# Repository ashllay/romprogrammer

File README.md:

# romprogrammer
Open Source Flash/EEPROM programmer

This is an open source programmer for 8 bit-wide parallel Flash/EEPROM chips. So far I've only tested it with (and hardcoded the software for) 2MBit (256Kx8) JEDEC compatible Flash chips (and designed the board layout accordingly).

Larger ROMs would require a redesign of the board, smaller ROMs require an adapter for the pinout.

The board uses an Arduino Nano onto which the firmware is flashed. Then you can read and write your PROMs using the command line tool (which should work on all POSIX systems, but I only tested on Debian Linux).

The board layout is single sided and uses relatively wide clearances and traces - ideal for DIY etching :)

## Schematic and Layout

Schematic and layout were made in [KiCad EDA](http://kicad-pcb.org/). You can use that to export to Gerber or PDF, whatever you prefer for you etching (or what you need for your professional board manufacturing service).

## Building

### Hardware
#### Parts

* Whatever PCB material you want to use
* 3x 74HC595 serial in, parallel out shift registers (Dual Inline Package)
* 1x 32 Pin JEDEC DIL chip socket (ZIF, if you want to make your life easier)
* 2x 15 Pin female pin headers (for the Arduino Nano)
* 1x Arduino Nano
* 1x 100nF ceramic capacitor, through hole
* a few centimeters of insulated jumper wire

The hardware is designed to be easily DIY etched. It only uses a single layer (+ a few jumper wires). The jumper wires are indicated on the front copper layer. You should also add a 100nF ceramic cap between pins 16 and 32 of the ROM socket to stabilize its power supply.

### Software
The software is split into two parts, the firmware for the ATMega328P (the µC on the Arduino Nano) and the Linux command line tool. 

#### Firmware

The firmware requires gcc-avr and [avr-libc](http://www.nongnu.org/avr-libc/). The Makefile also contains a rule for writing the firmware to the Arduino using avrdude. (Using an AVRISPmk2, if you want to use the built-in bootloader of the Arduino, you'll have to adapt the Makefile accordingly).

Just build the software in the firmware directory using make, flash it using make flash.

#### CLI

The Linux command line tool is compiled using CMake, goto the cli directory, create a build directory, cd into it, run cmake, then make:

```
mkdir build
cd build
cmake ..
make
```

### Usage
#### Basic Usage and Tests

The command line interface is relatively easy to use, because it doesn't offer many functions (yet). A first check if building has worked and communication between the host and the programmer is working, can be performed by using the ping command:

```
romprg /dev/ttyUSB0 ping
```

(You'll require read/write access to the USB serial port, usually by adding your user account to the dialout group).

This should tell you some information about the firmware and indicate that communication is working.

Next, you should verify that your PROM chip is detected correctly by using the id command:

```
romprg /dev/ttyUSB0 id
```

This will use the JEDEC identification system to query the vendor and device ID of your ROM chip, like this:

```
EEPROM chip identification: manufacturer=0xBF, device=0xB6
```

These should match the IDs noted in your EEPROM's device datasheet.

#### Erasing

You can erase the whole chip or individual sectors using the erase command:

```
romprg /dev/ttyUSB0 erase chip
```

to erase the whole chip, or 

```
romprg /dev/ttyUSB0 erase <startaddr> <endaddr>
```

to erase individual sectors. Note that the software only supports 4KByte sectors right now (the most common sector size in Flash chips).
endaddr must be the address of the byte _after_ the last byte to be erased. startaddr and endaddr must be sector aligned.

#### Writing

After erasing, you can write data to the chip by using the write command:

```
romprg /dev/ttyUSB0 write <startaddr> <inputfile>
```

At the moment only flat binary files are supported (i.e. the file content will be written verbatim to the flash). startaddr need not be sector aligned. startaddr + the size of inputfile must be smaller than the chip size.

#### Reading

You may also read back data on the chip using the read command:

```
romprg /dev/ttyUSB0 read <startaddr> <endaddr> <outfile>
```

endaddr must be greater than startaddr and indicates the address of the byte after the last one to be read. At the moment only flat binary files are supported, i.e. the ROM content will be copied verbatim into outfile. outfile will also be overwritten without asking you for permission, so make sure you know what you're doing ;-)

#### Verifying

There are two way to verify the contents of the ROM: the verify command, which reads a section of the ROM and compares it to an input file, and the crc command, which returns the CRC16 of a given ROM section.

```
romprg /dev/ttyUSB0 verify <startaddr> <endaddr> <infile>
```

Arguments are the same as for the read command (except the file is read instead of written).

```
romprg /dev/ttyUSB0 crc <startaddr> <endaddr>
```

Here, startaddr and endaddr work the same way as in the other commands.

## License
Copyright (c) 2017 Florian Keßeler

The whole software and hardware is released under the terms of the [GNU General Public License version 2](http://www.gnu.de/documents/gpl-2.0.en.html).

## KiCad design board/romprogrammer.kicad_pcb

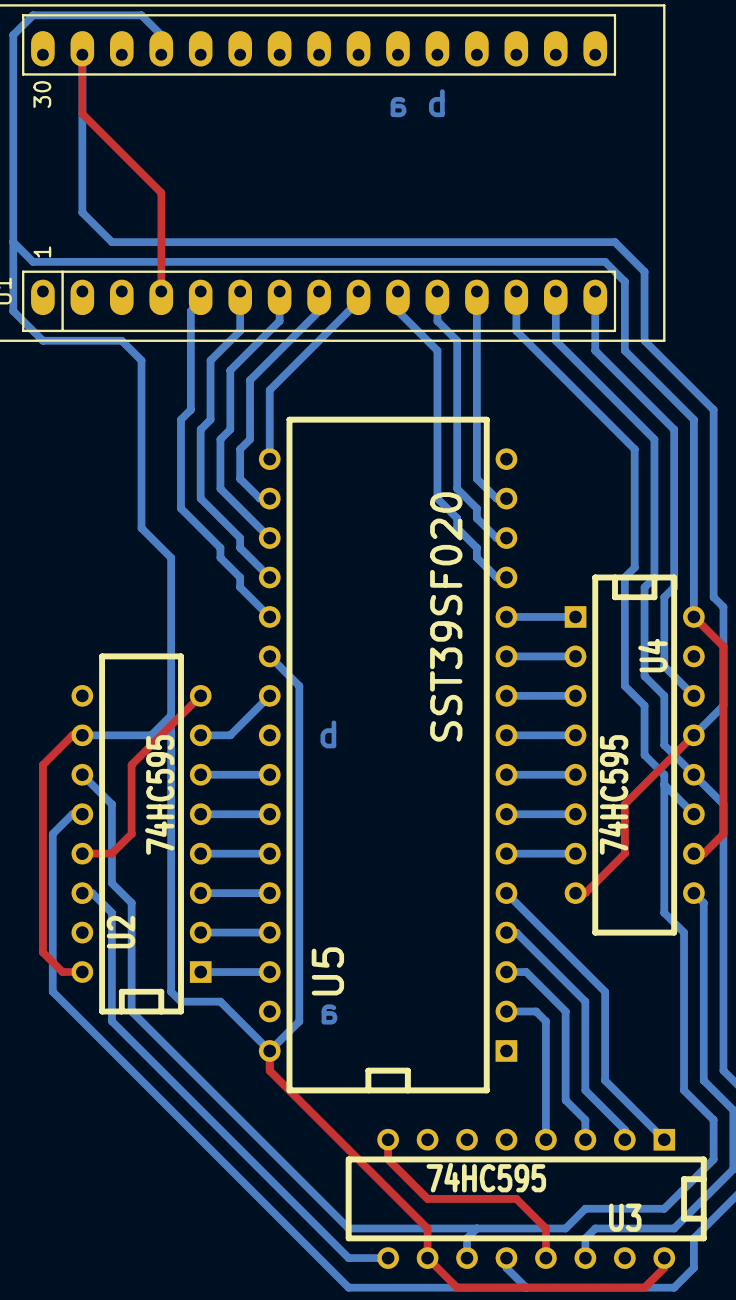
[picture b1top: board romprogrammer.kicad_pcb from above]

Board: 2 copper layers, 5 parts (0 on the bottom side), 35 nets.

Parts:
U1: ARDUINO_NANO_V3
U2, U3, U4: 74HC595; DIP-16__300
U5: SST39SF020; DIP-32__600

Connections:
/A0: U4.1, U5.12
/A1: U4.2, U5.11
/A2: U4.3, U5.10
/A3: U4.4, U5.9
/A4: U4.5, U5.8
/A5: U4.6, U5.7
/A6: U4.7, U5.6
/A7: U3.1, U5.5
/A8: U2.4, U5.27
/A9: U2.5, U5.26
/A10: U2.7, U5.23
/A11: U2.6, U5.25
/A12: U3.2, U5.4
/A13: U2.3, U5.28
/A14: U2.2, U5.29
/A15: U3.3, U5.3
/A16: U3.4, U5.2
/A17: U2.1, U5.30
/D0: U1.10, U5.13
/D1: U1.11, U5.14
/D2: U1.12, U5.15
/D3: U1.9, U5.17
/D4: U1.8, U5.18
/D5: U1.7, U5.19
/D6: U1.6, U5.20
/D7: U1.5, U5.21
/RCLK: U1.14, U2.12, U3.12, U4.12
/SRCLK: U1.13, U2.11, U3.11, U4.11
GND: U1.4, U1.29, U2.8, U2.13, U3.8, U3.13, U4.8, U4.13, U5.16
unnamed: U1.15, U4.14
unnamed: U2.14, U3.9
unnamed: U3.14, U4.9
OE: U1.20, U5.24
PGM: U1.21, U5.31
VCC: U1.27, U2.10, U2.16, U3.10, U3.16, U4.10, U4.16, U5.22, U5.32

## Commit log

2017-03-30 Added basic framework
2017-03-30 added make clean
2017-03-30 added gitignore
2017-03-30 Added all flash functionality (untested :-p)
2017-03-30 Started UART
2017-03-31 Cleaned up, implemented untested serial protocol
2017-03-31 Added all commands, now it's time to test the stuff
2017-03-31 Added board layout
2017-04-14 firmware seems to work so far :)
2017-04-14 Some cleanup and generalization
2017-04-14 more cleanup
2017-04-14 client side
2017-04-14 writing is working :)
2017-04-14 all functions working :)
2017-04-14 CLI almost done
2017-04-14 All commands implemented :)
2017-04-14 fixed board
2017-04-16 deleted build files
2017-05-04 work
